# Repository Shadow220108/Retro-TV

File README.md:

<<<<<<< HEAD
| Retro-TV |
| --- |
|  | 

Its a LED Matrix display of 7x7 LEDs, in a vintage television style case!  

### PCB
The PCB is designed to be compact with about 50 LEDs in just about 60mm of space
| LED Matrix |
| --- |
|  | 

| MCU |
| --- |
|  |

| PCB (All Layers)|
| --- |
|  |
| --- |
|  |

| PS : Some PCB art|
| --- |
|  |
| --- |
|  |
| --- |
|  |

## Case

The case is designed to be 3D printed and attached with magnets. The bottom case, top case, plate, and knob are all designed to be printed.

| CAD|
| --- |
|  |
| --- |
|  |

## BOM 
|Name                        |Purpose                                |Cost Per Item (USD)|Quantity|Total (USD)|Link                                                                                                                                                                                                                                                                                                                                                                                                                                                                                                          |Distributor     |
|----------------------------|---------------------------------------|-------------------|--------|-----------|--------------------------------------------------------------------------------------------------------------------------------------------------------------------------------------------------------------------------------------------------------------------------------------------------------------------------------------------------------------------------------------------------------------------------------------------------------------------------------------------------------------|----------------|
|3D Prints                   |to get prints from #printing-legion    |5.00               |1       |5.00       |                                                                                                                                                                                                                                                                                                                                                                                                                                                                                                              |#printing-legion|
|Soldering Hotplate          |To solder the mini leds                |0.00               |1       |0.00       |                                                                                                                                                                                                                                                                                                                                                                                                                                                                                                              |Self sourced    |
|Soldering paste             |to solder the smd components           |4.50               |1       |4.50       |https://www.amazon.in/gp/product/B0F9VTZJ5R?smid=A32I52VHFPY5IG&psc=1                                                                                                                                                                                                                                                                                                                                                                                                                                         |Amazon          |
|Alkin 65W adapter           |To use the soldering hotplate to solder|8.54               |1       |8.54       |https://www.amazon.in/AILKIN-Charging-Adapter-Multi-Port-Compatible/dp/B0GH81K2LK?crid=WF9QX765130Z&dib=eyJ2IjoiMSJ9.y109kyXIda8EdsX6DmyLc7Ct8sLh5g0dF3BTo2-PFvVzBm2er4SxHfDKU4Hr5NPA8yfTA9wzzGvEpIZqqoM65C-fW6aWJySmadJsd-KR7G0xMvxDkAgR5lkbsAFU4BAfi4bngmddfTHXbUTOggHFI3yQklGQg8kKB2kZIpbg_5mR9pZSpv4IxL0D5Nh6j2RvENrpHNuMKFqMFQ7vNoEfNMVAlhyqgAgMS-CQnSgDd_U.ipAeLdsmErAF3HJuhAX2E9gJ9zC4Vg1IA7Hfn_dZjtw&dib_tag=se&keywords=pd%2B65w%2Badapter&qid=1774040169&sprefix=pd%2B65w%2B%2Caps%2C375&sr=8-4&th=1|Amazon          |
|Neodimium magnets           |to attach the top and bottom case      |3.00               |1       |3.00       |https://www.amazon.in/gp/product/B0G2SW9GZL?smid=AP7MBNLZTN3FQ&psc=1                                                                                                                                                                                                                                                                                                                                                                                                                                          |amazon          |
|330 ohm resistor ( 10 moq ) |to not burst the leds                  |0.11               |1       |0.11       |https://robu.in/product/330-ohm-1w-metal-film-resistor-pack-of-40/                                                                                                                                                                                                                                                                                                                                                                                                                                            |robu.in         |
|1000uF capacitor            |Bulk capacitor                         |0.11               |1       |0.11       |https://robu.in/product/1000uf-25v-electrolytic-capacitor-dip-pack-of-5/                                                                                                                                                                                                                                                                                                                                                                                                                                      |robu.in         |
|0.1uF capacitors            |to reduce electrical noise             |0.07               |50      |3.75       |https://probots.co.in/0-1-uf-50v-smd-ceramic-capacitor-0603-package.html                                                                                                                                                                                                                                                                                                                                                                                                                                      |probots.co      |
|74AHCT1G125GV               |Level shifter for LEDs                 |0.16               |1       |0.16       |https://robu.in/product/74ahct1g125gv125-nexperia-1-8ma-4-5v5-5v-8ma-1-sot-753-buffers-drivers-receivers-transceivers-rohs/                                                                                                                                                                                                                                                                                                                                                                                   |robu,in         |
|SMD 5050 LEDs               |For the display                        |0.04               |50      |2.00       |https://www.flyrobo.in/5050-red-green-blue-rgb-smd-led                                                                                                                                                                                                                                                                                                                                                                                                                                                        |flyrobo.in      |
|ESP32 Devboard              |MCU to control the LEDs                |4.62               |1       |4.62       |https://www.flyrobo.in/esp-wroom-32-nodemcu-module?search=esp32&description=true                                                                                                                                                                                                                                                                                                                                                                                                                              |flyrobo.in      |
|PCB ( 5 MOQ )               |to solder all the components           |13.02              |1       |13.02      |                                                                                                                                                                                                                                                                                                                                                                                                                                                                                                              |JLCPCB          |
=======
| Retro-TV |
| --- |
|  | 

Its a LED Matrix display of 7x7 LEDs, in a vintage television style case!  

### PCB
The PCB is designed to be compact with about 50 LEDs in just about 60mm of space
| LED Matrix |
| --- |
|  | 

| MCU |
| --- |
|  |

| PCB (All Layers)|
| --- |
|  |
| --- |
|  |

| PS : Some PCB art|
| --- |
|  |
| --- |
|  |
| --- |
|  |

## Case

The case is designed to be 3D printed and attached with magnets. The bottom case, top case, plate, and knob are all designed to be printed.

| CAD|
| --- |
|  |
| --- |
|  |

## BOM 
|Name                        |Purpose                                |Cost Per Item (USD)|Quantity|Total (USD)|Link                                                                                                                                                                                                                                                                                                                                                                                                                                                                                                          |Distributor     |
|----------------------------|---------------------------------------|-------------------|--------|-----------|--------------------------------------------------------------------------------------------------------------------------------------------------------------------------------------------------------------------------------------------------------------------------------------------------------------------------------------------------------------------------------------------------------------------------------------------------------------------------------------------------------------|----------------|
|3D Prints                   |to get prints from #printing-legion    |5.00               |1       |5.00       |                                                                                                                                                                                                                                                                                                                                                                                                                                                                                                              |#printing-legion|
|Soldering Hotplate          |To solder the mini leds                |0.00               |1       |0.00       |                                                                                                                                                                                                                                                                                                                                                                                                                                                                                                              |Self sourced    |
|Soldering paste             |to solder the smd components           |4.50               |1       |4.50       |https://www.amazon.in/gp/product/B0F9VTZJ5R?smid=A32I52VHFPY5IG&psc=1                                                                                                                                                                                                                                                                                                                                                                                                                                         |Amazon          |
|Alkin 65W adapter           |To use the soldering hotplate to solder|8.54               |1       |8.54       |https://www.amazon.in/AILKIN-Charging-Adapter-Multi-Port-Compatible/dp/B0GH81K2LK?crid=WF9QX765130Z&dib=eyJ2IjoiMSJ9.y109kyXIda8EdsX6DmyLc7Ct8sLh5g0dF3BTo2-PFvVzBm2er4SxHfDKU4Hr5NPA8yfTA9wzzGvEpIZqqoM65C-fW6aWJySmadJsd-KR7G0xMvxDkAgR5lkbsAFU4BAfi4bngmddfTHXbUTOggHFI3yQklGQg8kKB2kZIpbg_5mR9pZSpv4IxL0D5Nh6j2RvENrpHNuMKFqMFQ7vNoEfNMVAlhyqgAgMS-CQnSgDd_U.ipAeLdsmErAF3HJuhAX2E9gJ9zC4Vg1IA7Hfn_dZjtw&dib_tag=se&keywords=pd%2B65w%2Badapter&qid=1774040169&sprefix=pd%2B65w%2B%2Caps%2C375&sr=8-4&th=1|Amazon          |
|Neodimium magnets           |to attach the top and bottom case      |3.00               |1       |3.00       |https://www.amazon.in/gp/product/B0G2SW9GZL?smid=AP7MBNLZTN3FQ&psc=1                                                                                                                                                                                                                                                                                                                                                                                                                                          |amazon          |
|330 ohm resistor ( 10 moq ) |to not burst the leds                  |0.11               |1       |0.11       |https://robu.in/product/330-ohm-1w-metal-film-resistor-pack-of-40/                                                                                                                                                                                                                                                                                                                                                                                                                                            |robu.in         |
|1000uF capacitor            |Bulk capacitor                         |0.11               |1       |0.11       |https://robu.in/product/1000uf-25v-electrolytic-capacitor-dip-pack-of-5/                                                                                                                                                                                                                                                                                                                                                                                                                                      |robu.in         |
|0.1uF capacitors            |to reduce electrical noise             |0.07               |50      |3.75       |https://probots.co.in/0-1-uf-50v-smd-ceramic-capacitor-0603-package.html                                                                                                                                                                                                                                                                                                                                                                                                                                      |probots.co      |
|74AHCT1G125GV               |Level shifter for LEDs                 |0.16               |1       |0.16       |https://robu.in/product/74ahct1g125gv125-nexperia-1-8ma-4-5v5-5v-8ma-1-sot-753-buffers-drivers-receivers-transceivers-rohs/                                                                                                                                                                                                                                                                                                                                                                                   |robu,in         |
|SMD 5050 LEDs               |For the display                        |0.04               |50      |2.00       |https://www.flyrobo.in/5050-red-green-blue-rgb-smd-led                                                                                                                                                                                                                                                                                                                                                                                                                                                        |flyrobo.in      |
|ESP32 Devboard              |MCU to control the LEDs                |4.62               |1       |4.62       |https://www.flyrobo.in/esp-wroom-32-nodemcu-module?search=esp32&description=true                                                                                                                                                                                                                                                                                                                                                                                                                              |flyrobo.in      |
|PCB ( 5 MOQ )               |to solder all the components           |13.02              |1       |13.02      |                                                                                                                                                                                                                                                                                                                                                                                                                                                                                                              |JLCPCB          |
>>>>>>> c8a452447a518745ea2085dd8981138584917547

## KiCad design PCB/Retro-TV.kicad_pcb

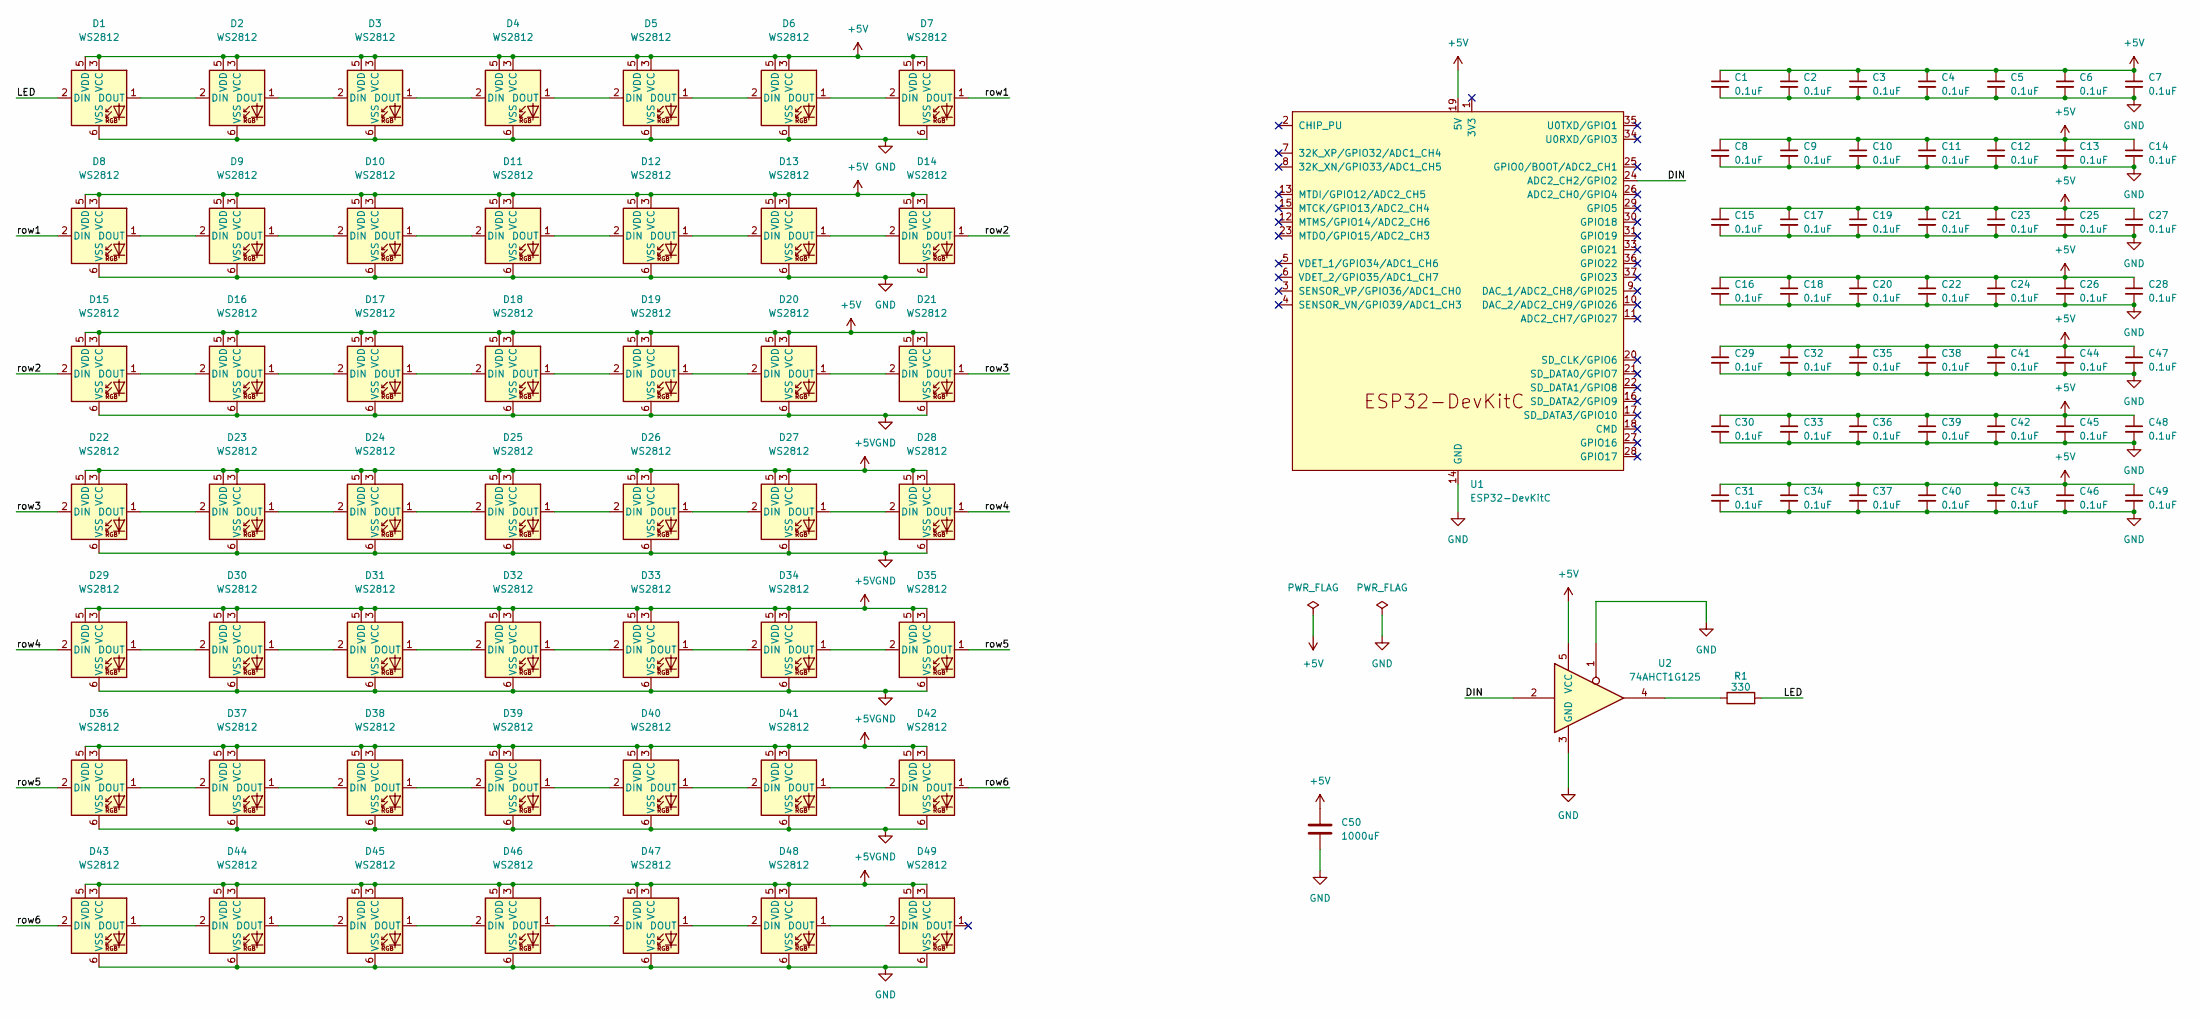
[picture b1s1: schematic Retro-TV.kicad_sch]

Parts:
C1, C2, C3, C4, C5, C6, C7, C8, C9, C10, C11, C12, C13, C14, C15, C16, C17, C18, C19, C20, C21, C22, C23, C24, C25, C26, C27, C28, C29, C30, C31, C32, C33, C34, C35, C36, C37, C38, C39, C40, C41, C42, C43, C44, C45, C46, C47, C48, C49: 0.1uF; C_0603_1608Metric_Pad1.08x0.95mm_HandSolder
C50: 1000uF; CP_Radial_D10.0mm_P5.00mm
D1, D2, D3, D4, D5, D6, D7, D8, D9, D10, D11, D12, D13, D14, D15, D16, D17, D18, D19, D20, D21, D22, D23, D24, D25, D26, D27, D28, D29, D30, D31, D32, D33, D34, D35, D36, D37, D38, D39, D40, D41, D42, D43, D44, D45, D46, D47, D48, D49: WS2812; LED_WS2812_PLCC6_5.0x5.0mm_P1.6mm
R1: 330; R_Axial_DIN0207_L6.3mm_D2.5mm_P7.62mm_Horizontal
U1: ESP32-DevKitC
U2: 74AHCT1G125; SOT-23-5_HandSoldering

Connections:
+5V: C1.1, C2.1, C3.1, C4.1, C5.1, C6.1, C7.1, C8.1, C9.1, C10.1, C11.1, C12.1, C13.1, C14.1, C15.1, C16.1, C17.1, C18.1, C19.1, C20.1, C21.1, C22.1, C23.1, C24.1, C25.1, C26.1, C27.1, C28.1, C29.1, C30.1, C31.1, C32.1, C33.1, C34.1, C35.1, C36.1, C37.1, C38.1, C39.1, C40.1, C41.1, C42.1, C43.1, C44.1, C45.1, C46.1, C47.1, C48.1, C49.1, C50.1, D1.3 (VCC), D1.5 (VDD), D2.3 (VCC), D2.5 (VDD), D3.3 (VCC), D3.5 (VDD), D4.3 (VCC), D4.5 (VDD), D5.3 (VCC), D5.5 (VDD), D6.3 (VCC), D6.5 (VDD), D7.3 (VCC), D7.5 (VDD), D8.3 (VCC), D8.5 (VDD), D9.3 (VCC), D9.5 (VDD), D10.3 (VCC), D10.5 (VDD), D11.3 (VCC), D11.5 (VDD), D12.3 (VCC), D12.5 (VDD), D13.3 (VCC), D13.5 (VDD), D14.3 (VCC), D14.5 (VDD), D15.3 (VCC), D15.5 (VDD), D16.3 (VCC), D16.5 (VDD), D17.3 (VCC), D17.5 (VDD), D18.3 (VCC), D18.5 (VDD), D19.3 (VCC), D19.5 (VDD), D20.3 (VCC), D20.5 (VDD), D21.3 (VCC), D21.5 (VDD), D22.3 (VCC), D22.5 (VDD), D23.3 (VCC), D23.5 (VDD), D24.3 (VCC), D24.5 (VDD), D25.3 (VCC), D25.5 (VDD), D26.3 (VCC), D26.5 (VDD), D27.3 (VCC), D27.5 (VDD), D28.3 (VCC), D28.5 (VDD), D29.3 (VCC), D29.5 (VDD), D30.3 (VCC), D30.5 (VDD), D31.3 (VCC), D31.5 (VDD), D32.3 (VCC), D32.5 (VDD), D33.3 (VCC), D33.5 (VDD), D34.3 (VCC), D34.5 (VDD), D35.3 (VCC), D35.5 (VDD), D36.3 (VCC), D36.5 (VDD), D37.3 (VCC), D37.5 (VDD), D38.3 (VCC), D38.5 (VDD), D39.3 (VCC), D39.5 (VDD), D40.3 (VCC), D40.5 (VDD), D41.3 (VCC), D41.5 (VDD), D42.3 (VCC), D42.5 (VDD), D43.3 (VCC), D43.5 (VDD), D44.3 (VCC), D44.5 (VDD), D45.3 (VCC), D45.5 (VDD), D46.3 (VCC), D46.5 (VDD), D47.3 (VCC), D47.5 (VDD), D48.3 (VCC), D48.5 (VDD), D49.3 (VCC), D49.5 (VDD), U1.19 (5V), U2.5 (VCC)
/DIN: U1.24 (ADC2_CH2/GPIO2), U2.2
/LED: D1.2 (DIN), R1.2
/row1: D7.1 (DOUT), D8.2 (DIN)
/row2: D14.1 (DOUT), D15.2 (DIN)
/row3: D21.1 (DOUT), D22.2 (DIN)
/row4: D28.1 (DOUT), D29.2 (DIN)
/row5: D35.1 (DOUT), D36.2 (DIN)
/row6: D42.1 (DOUT), D43.2 (DIN)
GND: C1.2, C2.2, C3.2, C4.2, C5.2, C6.2, C7.2, C8.2, C9.2, C10.2, C11.2, C12.2, C13.2, C14.2, C15.2, C16.2, C17.2, C18.2, C19.2, C20.2, C21.2, C22.2, C23.2, C24.2, C25.2, C26.2, C27.2, C28.2, C29.2, C30.2, C31.2, C32.2, C33.2, C34.2, C35.2, C36.2, C37.2, C38.2, C39.2, C40.2, C41.2, C42.2, C43.2, C44.2, C45.2, C46.2, C47.2, C48.2, C49.2, C50.2, D1.6 (VSS), D2.6 (VSS), D3.6 (VSS), D4.6 (VSS), D5.6 (VSS), D6.6 (VSS), D7.6 (VSS), D8.6 (VSS), D9.6 (VSS), D10.6 (VSS), D11.6 (VSS), D12.6 (VSS), D13.6 (VSS), D14.6 (VSS), D15.6 (VSS), D16.6 (VSS), D17.6 (VSS), D18.6 (VSS), D19.6 (VSS), D20.6 (VSS), D21.6 (VSS), D22.6 (VSS), D23.6 (VSS), D24.6 (VSS), D25.6 (VSS), D26.6 (VSS), D27.6 (VSS), D28.6 (VSS), D29.6 (VSS), D30.6 (VSS), D31.6 (VSS), D32.6 (VSS), D33.6 (VSS), D34.6 (VSS), D35.6 (VSS), D36.6 (VSS), D37.6 (VSS), D38.6 (VSS), D39.6 (VSS), D40.6 (VSS), D41.6 (VSS), D42.6 (VSS), D43.6 (VSS), D44.6 (VSS), D45.6 (VSS), D46.6 (VSS), D47.6 (VSS), D48.6 (VSS), D49.6 (VSS), U1.14 (GND), U1.32 (GND), U1.38 (GND), U2.1, U2.3 (GND)
unnamed: D1.1 (DOUT), D2.2 (DIN)
unnamed: D2.1 (DOUT), D3.2 (DIN)
unnamed: D3.1 (DOUT), D4.2 (DIN)
unnamed: D4.1 (DOUT), D5.2 (DIN)
unnamed: D5.1 (DOUT), D6.2 (DIN)
unnamed: D6.1 (DOUT), D7.2 (DIN)
unnamed: D8.1 (DOUT), D9.2 (DIN)
unnamed: D9.1 (DOUT), D10.2 (DIN)
unnamed: D10.1 (DOUT), D11.2 (DIN)
unnamed: D11.1 (DOUT), D12.2 (DIN)
unnamed: D12.1 (DOUT), D13.2 (DIN)
unnamed: D13.1 (DOUT), D14.2 (DIN)
unnamed: D15.1 (DOUT), D16.2 (DIN)
unnamed: D16.1 (DOUT), D17.2 (DIN)
unnamed: D17.1 (DOUT), D18.2 (DIN)
unnamed: D18.1 (DOUT), D19.2 (DIN)
unnamed: D19.1 (DOUT), D20.2 (DIN)
unnamed: D20.1 (DOUT), D21.2 (DIN)
unnamed: D22.1 (DOUT), D23.2 (DIN)
unnamed: D23.1 (DOUT), D24.2 (DIN)
unnamed: D24.1 (DOUT), D25.2 (DIN)
unnamed: D25.1 (DOUT), D26.2 (DIN)
unnamed: D26.1 (DOUT), D27.2 (DIN)
unnamed: D27.1 (DOUT), D28.2 (DIN)
unnamed: D29.1 (DOUT), D30.2 (DIN)
unnamed: D30.1 (DOUT), D31.2 (DIN)
unnamed: D31.1 (DOUT), D32.2 (DIN)
unnamed: D32.1 (DOUT), D33.2 (DIN)
unnamed: D33.1 (DOUT), D34.2 (DIN)
unnamed: D34.1 (DOUT), D35.2 (DIN)
unnamed: D36.1 (DOUT), D37.2 (DIN)
unnamed: D37.1 (DOUT), D38.2 (DIN)
unnamed: D38.1 (DOUT), D39.2 (DIN)
unnamed: D39.1 (DOUT), D40.2 (DIN)
unnamed: D40.1 (DOUT), D41.2 (DIN)
unnamed: D41.1 (DOUT), D42.2 (DIN)
unnamed: D43.1 (DOUT), D44.2 (DIN)
unnamed: D44.1 (DOUT), D45.2 (DIN)
unnamed: D45.1 (DOUT), D46.2 (DIN)
unnamed: D46.1 (DOUT), D47.2 (DIN)
unnamed: D47.1 (DOUT), D48.2 (DIN)
unnamed: D48.1 (DOUT), D49.2 (DIN)
unnamed: R1.1, U2.4

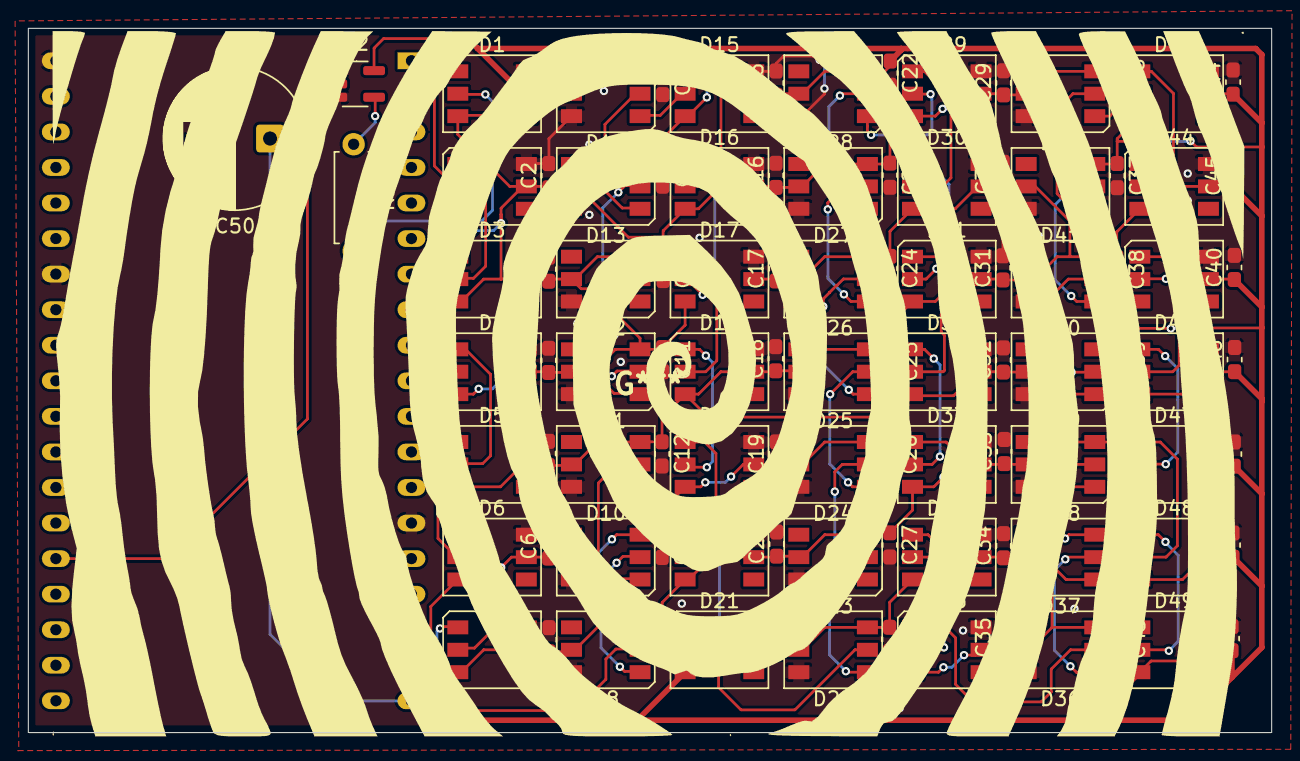
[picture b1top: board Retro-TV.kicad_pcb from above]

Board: 2 copper layers, 88.8 x 50.3 mm, 102 parts (1 on the bottom side), 53 nets.

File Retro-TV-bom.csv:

Name,Purpose,Cost Per Item (USD),Quantity,Total (USD),Link,Distributor
"3D Prints","to get prints from #printing-legion",5.00,1,5.00,"","#printing-legion"
"Soldering Hotplate","To solder the mini leds",0.00,1,0.00,"","Self sourced "
"Soldering paste","to solder the smd components",4.50,1,4.50,"https://www.amazon.in/gp/product/B0F9VTZJ5R?smid=A32I52VHFPY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","Amazon"
"Alkin 65W adapter","To use the soldering hotplate to solder",8.54,1,8.54,"https://www.amazon.in/AILKIN-Charging-Adapter-Multi-Port-Com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","Amazon"
"Neodimium magnets","to attach the top and bottom case",3.00,1,3.00,"https://www.amazon.in/gp/product/B0G2SW9GZL?smid=AP7MBNLZTN3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","amazon"
"330 ohm resistor ( 10 moq ) ","to not burst the leds ",0.11,1,0.11,"https://robu.in/product/330-ohm-1w-metal-film-resistor-pack-of-40/","robu.in"
"1000uF capacitor","Bulk capacitor",0.11,1,0.11,"https://robu.in/product/1000uf-25v-electrolytic-capacitor-di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","robu.in"
"0.1uF capacitors","to reduce electrical noise",0.07,50,3.75,"https://probots.co.in/0-1-uf-50v-smd-ceramic-capacitor-0603-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","probots.co"
"74AHCT1G125GV","Level shifter for LEDs",0.16,1,0.16,"https://robu.in/product/74ahct1g125gv125-nexperia-1-8ma-4-5v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","robu,in"
"SMD 5050 LEDs","For the display",0.04,50,2.00,"https://www.flyrobo.in/5050-red-green-blue-rgb-smd-led","flyrobo.in"
"ESP32 Devboard","MCU to control the LEDs",4.62,1,4.62,"https://www.flyrobo.in/esp-wroom-32-nodemcu-module?search=es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","flyrobo.in"
"PCB ( 5 MOQ )","to solder all the components ",13.02,1,13.02,"","JLCPCB"

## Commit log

2026-03-20 Upload files from local repo
2026-03-20 Rename Blue Retro Video Game List Youtube Thumbnail.png to banner.png
2026-03-20 Added Firmware
2026-03-20 Added production
